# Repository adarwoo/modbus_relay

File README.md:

# Modbus Relay with EStop  #

## Introduction
This project features is a MODBUS RTU relays controller, which includes failsafe mode and an EStop.
It is aimed for industrial systems such as a CNC or equivalent.

The project comes complete with documentation, schematic, PCB, 3D part, artwork and source code.

For operational documentation, please check the complete [User Manual](docs/user_manual.md)

---

## Features summary

1. Standard DIN Rail mountable PCB
2. 3 relays - 9.4A 250VAC per output
3. Operational integrity minded
   * Uses a safety relay with force conduits and read back
   * Infeed voltage measurement with acceptable range
   * Communication watchdog
4. EStop management
   * Used for failsafe of the relay operation
      * Relay failure
      * Infeed voltage out-of-range
      * Communication loss
   * Externally controlled
     * Pulsed EStop
     * Resetable
     * Terminal
6. Operational statistics
   * Number of cycles
   * Running time
   * Fault codes

## Presentation of the hardware

<div style="text-align: center; position: relative;">

</div>

At the core of the relay is an AVR Tiny3227, an automotive grade MPU designed for harsh environment.
The MPU is clocked using the internal calibrated RC clock at 20MHz.

The relays are SISF brand used in safety critical applications.
They feature a forced conduit (so all contacts are driven by the same bar) and a dedicated read-back contact.
This allow validating the correct relay operations.
The relay are driven by small MOSFET. The read back features a contact scrubbing circuit as recommended by the manufacturer.

The modbus interface uses a RS485 driver LTC1785A (which features short protection) and transient suppressors.

The relay output features MOV suppressors for inductive loads.

The PCB can be placed in a DIN Rail PCB mount. 4 mounting screws can also be used.
A 3D cover is available to cover the whole PCBs. Together with the DIN rail mount assembly, the module should comply with IP2X.

### CAD files

The following files are available:
 * The [schematic](hw/modbus_relay.kicad.sch) edited with *KiCAD 9.1*
 * The [PCB](hw/modbus_relay.kicad.pcb) edited in *KiCAD 9.1*
 * The [BOM](hw/BOM.md) edited in *KiCAD 9.1*
 * The [Front plate artwork](hw/front_plate_graphics.svg) edited in LibreOffice Draw
 * [The front plate STL file](cad/Front%20Plate.3mf)
 * [LED holder STL file](cad/leds_spacer.STL)
 * [Spacer columns STL file](cad/3mm%2016mm.STL)
 * [Flex swtich membrane](cad/Flex%20switch%20membrane.STL)
 * [Flex retaining holder](cad/Flex%20Holder.STL)

For printing instructions, refer to [Printing the Files](#printing-the-files).

#### Printing the files

 * The case was printed in mate green PLA with PLA support material for the AVR port.
 * The flexible switch was printed in TPU.
 * The holder in black PLA.

#### Printing the front plate

 * The front was printed on an adhesive vinyl sticker at max resolution then cut to size.

> [!Note]
> You may need to adjust the dimension to account for non-linearity of the printer.

## Presentation of the software
The software is build on top of a small framework revolving around a simple reactor pattern.
The reactor allow for an arbitrary function to be notified from any context, and will execute when the CPU become available.
A simple priority system allow for reactor functions to be called in priority (to process data in a register).

A dedicated reactor pin allows measuring the worse compute time for any reactor function, which in turn, determine the worse
case latency. This allow garanteeing a real time operation throughout.
As such, the system does handle all asynchronous events in realtime with no delay, including all Modbus transaction, even at 115200 Bauds.
The jitter on the RS485 is almost null, and all replies are instantanous (4ms delay to allow for proper end of frame detection).

A python scripts is used to generates the final source for the modbus functions.

> [!TIP]
> This project could be reused for other Modbus devices. A modbus interface generator is provided that makes adding modbus commands simple.

## Application software
The application software is written in C++23 as it uses meta programming, constant expressions and concepts for efficient code.<br/>
A <i>docker</i> file is provided to create a build environment.</br>
The code fits the 32Kb flash space with plenty spare.

For build instructions, see [How to Build](#how-to-build).

## Hardware
The schematic and PCB have been edited in KiCad 9 and are supplied too.

## How to build
A docker container file is provided to recreated a full build environment.<br/>
The application can also be built in Microchip studio.<br/>
You will need a Linux shell, or WSL shell in Windows.
The tool 'gitman' is required as well as Docker. (docker-ce or else).

### Steps
```bash
# Clone this repo
$ git clone https://https://github.com/adarwoo/modbus_relay.git
$ cd modbus_relay
# Optional - install gitman
$ pipx install gitman
$ gitman update
$ make NDEBUG=1 # Optional, add ARCH=attiny1624 to suit you device
```

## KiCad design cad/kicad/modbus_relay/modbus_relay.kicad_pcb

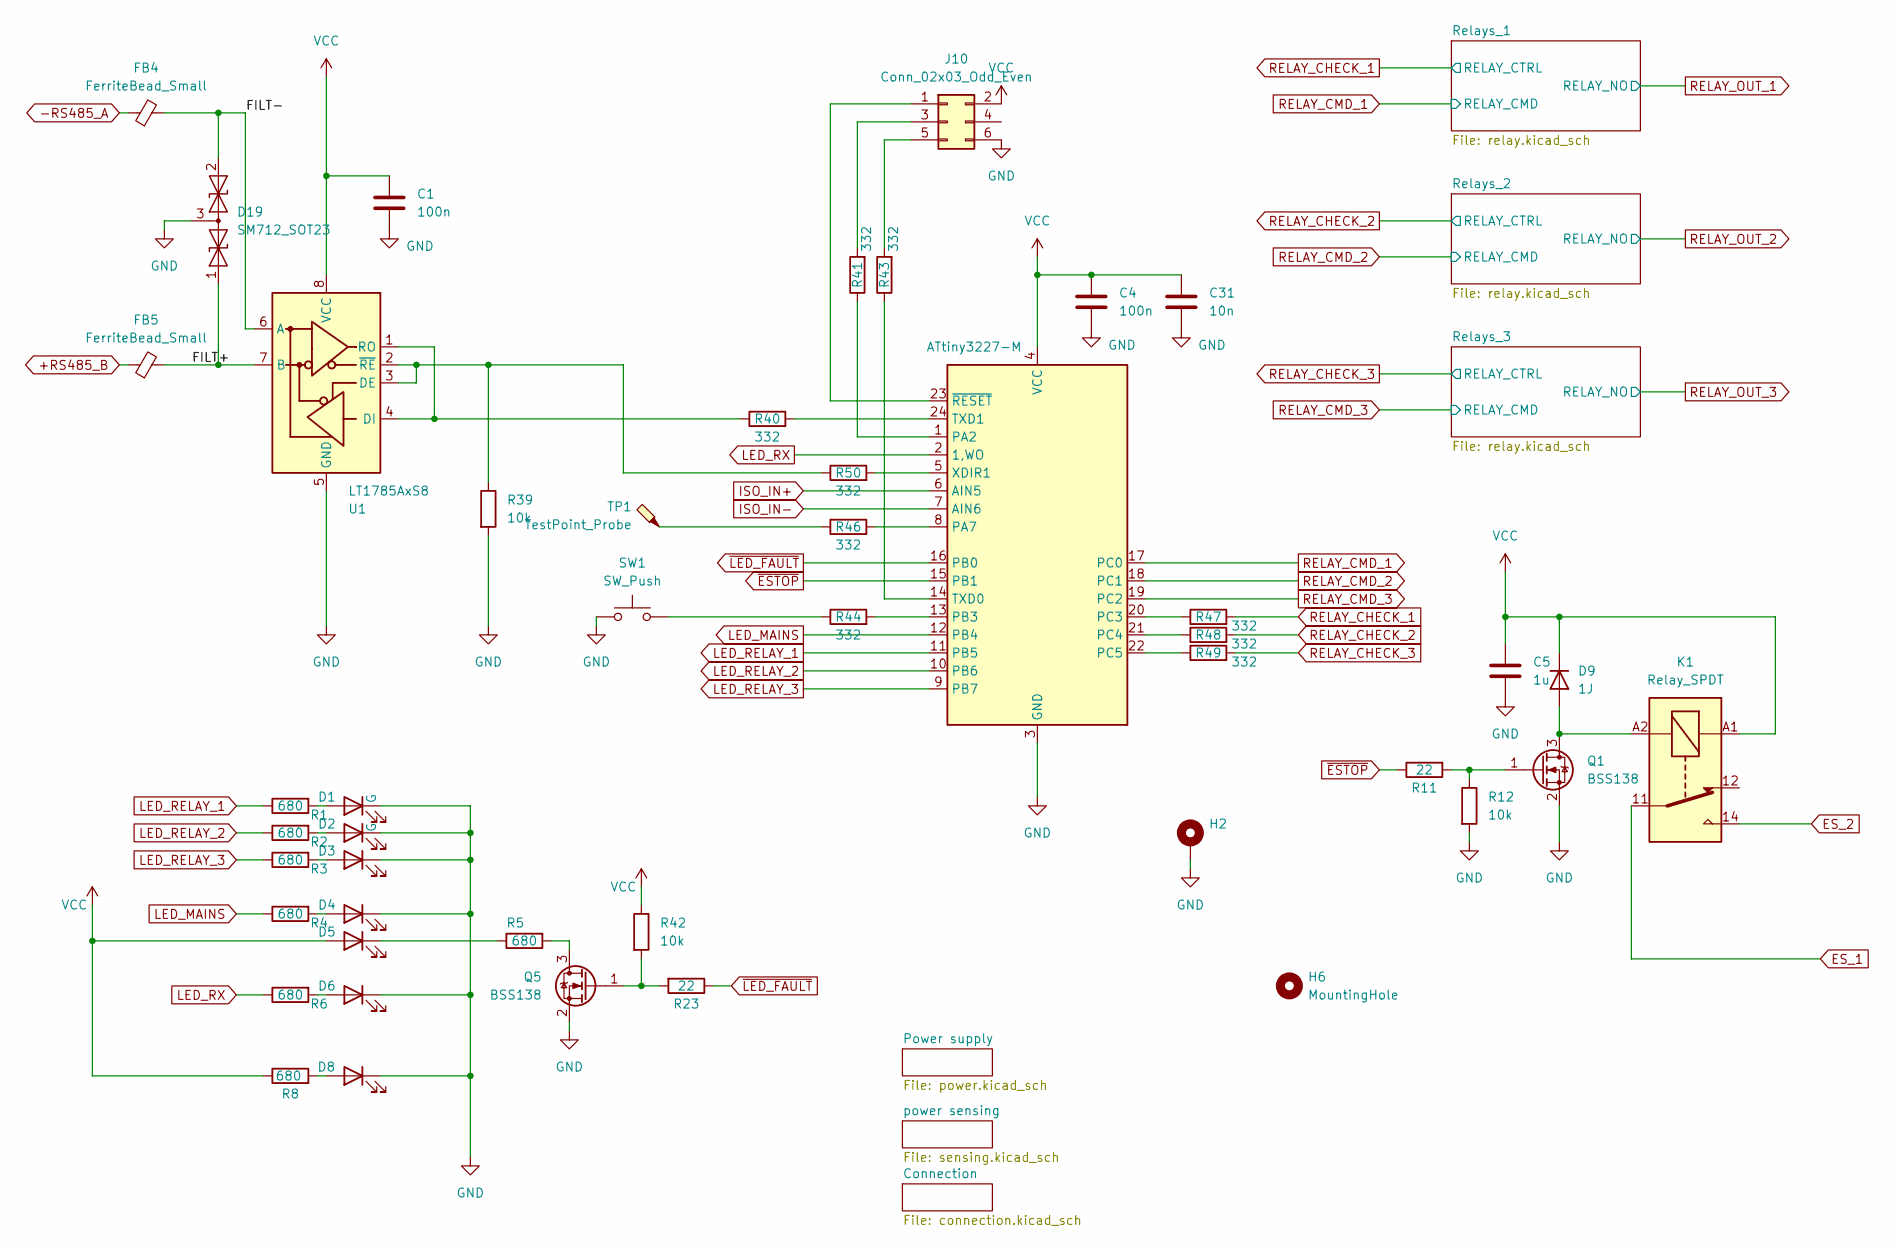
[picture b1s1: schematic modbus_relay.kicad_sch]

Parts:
C1, C4: 100n; C_0805_2012Metric_Pad1.18x1.45mm_HandSolder
C5: 1u; C_0805_2012Metric_Pad1.18x1.45mm_HandSolder
C31: 10n; C_0805_2012Metric_Pad1.18x1.45mm_HandSolder
D1, D2, D3, D4, D5, D6: G; LED_D3.0mm
D8: LED; LED_D3.0mm
D9: 1J; D_SOD-323_HandSoldering
D19: SM712_SOT23; SOT-23
FB4, FB5: FerriteBead_Small; L_0805_2012Metric
H2: MountingHole_Pad; MountingHole_3.2mm_M3_DIN965_Pad_TopBottom
H6: MountingHole; MountingHole_3.2mm_M3
J10: Conn_02x03_Odd_Even; PinHeader_2x03_P2.54mm_Vertical
K1: Relay_SPDT; Relay_SPDT_Finder_32.21-x000
Q1, Q5: BSS138; SOT-23
R1, R2, R3, R4, R5, R6, R8: 680; R_0805_2012Metric_Pad1.20x1.40mm_HandSolder
R11, R23: 22; R_0805_2012Metric_Pad1.20x1.40mm_HandSolder
R12, R39, R42: 10k; R_0805_2012Metric_Pad1.20x1.40mm_HandSolder
R40, R41, R43, R44, R46, R47, R48, R49, R50: 332; R_0805_2012Metric_Pad1.20x1.40mm_HandSolder
SW1: SW_Push; SW_PUSH_6mm_H4.3mm
TP1: TestPoint_Probe; TestPoint_Pad_D1.5mm
U1: LT1785AxS8; SOIC-8_3.9x4.9mm_P1.27mm
U2: ATtiny3227-M; QFN-24-1EP_4x4mm_P0.5mm_EP2.6x2.6mm

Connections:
+RS485_B: FB5.1; also elsewhere on the board
-RS485_A: FB4.1; also elsewhere on the board
/FILT+: D19.1 (A1), FB5.2, U1.7 (B)
/FILT-: D19.2 (A2), FB4.2, U1.6 (A)
ES_1: K1.11; also elsewhere on the board
ES_2: K1.14; also elsewhere on the board
GND: C1.2, C4.2, C5.2, C31.2, D1.1 (K), D2.1 (K), D3.1 (K), D4.1 (K), D6.1 (K), D8.1 (K), D19.3 (common), H2.1, J10.6, Q1.2 (S), Q5.2 (S), R12.2, R39.2, SW1.2, U1.5 (GND), U2.3 (GND), U2.25 (GND); also elsewhere on the board
ISO_IN+: U2.6 (AIN5); also elsewhere on the board
ISO_IN-: U2.7 (AIN6); also elsewhere on the board
LED_MAINS: R4.1, U2.12 (PB4)
LED_RELAY_1: R1.1, U2.11 (PB5)
LED_RELAY_2: R2.1, U2.10 (PB6)
LED_RELAY_3: R3.1, U2.9 (PB7)
LED_RX: R6.1, U2.2 (1,WO)
unnamed: D1.2 (A), R1.2
unnamed: D2.2 (A), R2.2
unnamed: D3.2 (A), R3.2
unnamed: D4.2 (A), R4.2
unnamed: D5.1 (K), R5.1
unnamed: D6.2 (A), R6.2
unnamed: D8.2 (A), R8.2
unnamed: D9.2 (A), K1.A2, Q1.3 (D)
unnamed: J10.1, U2.23 (~RESET)
unnamed: J10.3, R41.2
unnamed: J10.5, R43.2
unnamed: Q1.1 (G), R11.2, R12.1
unnamed: Q5.3 (D), R5.2
unnamed: Q5.1 (G), R23.2, R42.2
unnamed: R44.1, SW1.1
unnamed: R46.1, TP1.1
unnamed: R39.1, R50.1, U1.2 (~RE), U1.3 (DE)
unnamed: R40.1, U1.1 (RO), U1.4 (DI)
unnamed: R40.2, U2.24 (TXD1)
unnamed: R41.1, U2.1 (PA2)
unnamed: R50.2, U2.5 (XDIR1)
unnamed: R46.2, U2.8 (PA7)
unnamed: R43.1, U2.14 (TXD0)
unnamed: R44.2, U2.13 (PB3)
unnamed: R47.1, U2.20 (PC3)
unnamed: R48.1, U2.21 (PC4)
unnamed: R49.1, U2.22 (PC5)
RELAY_CHECK_1: R47.2; also elsewhere on the board
RELAY_CHECK_2: R48.2; also elsewhere on the board
RELAY_CHECK_3: R49.2; also elsewhere on the board
RELAY_CMD_1: U2.17 (PC0); also elsewhere on the board
RELAY_CMD_2: U2.18 (PC1); also elsewhere on the board
RELAY_CMD_3: U2.19 (PC2); also elsewhere on the board
VCC: C1.1, C4.1, C5.1, C31.1, D5.2 (A), D9.1 (K), J10.2, K1.A1, R8.1, R42.1, U1.8 (VCC), U2.4 (VCC); also elsewhere on the board
~ESTOP: R11.1, U2.15 (PB1)
~LED_FAULT: R23.1, U2.16 (PB0)

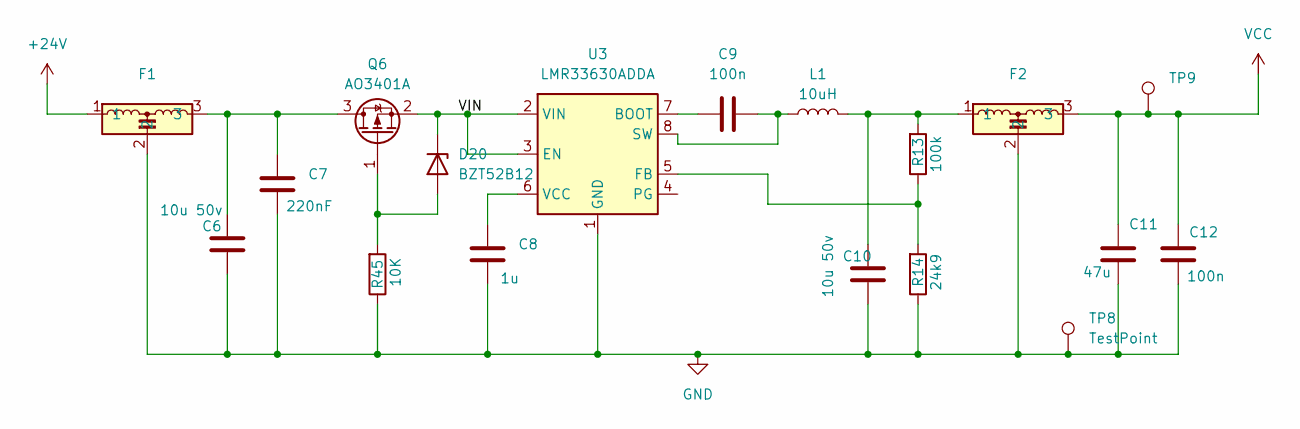
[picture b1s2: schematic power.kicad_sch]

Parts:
C6, C10: 10u 50v; C_1210_3225Metric_Pad1.33x2.70mm_HandSolder
C7: 220nF; C_0805_2012Metric_Pad1.18x1.45mm_HandSolder
C8: 1u; C_0805_2012Metric_Pad1.18x1.45mm_HandSolder
C9, C12: 100n; C_0805_2012Metric_Pad1.18x1.45mm_HandSolder
C11: 47u; C_1210_3225Metric_Pad1.33x2.70mm_HandSolder
D20: BZT52B12; D_SOD-123F
F1, F2: Murata_NFM61R
L1: 10uH; L_Bourns_SRP6060FA
Q6: AO3401A; SOT-23
R13: 100k; R_0805_2012Metric_Pad1.20x1.40mm_HandSolder
R14: 24k9; R_0805_2012Metric_Pad1.20x1.40mm_HandSolder
R45: 10K; R_0805_2012Metric_Pad1.20x1.40mm_HandSolder
TP8: TestPoint; TestPoint_Loop_D3.50mm_Drill0.9mm_Beaded
TP9: TestPoint; TestPoint_Pad_D1.5mm
U3: LMR33630ADDA; Texas_HSOP-8-1EP_3.9x4.9mm_P1.27mm_ThermalVias

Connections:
+24V: F1.1; also elsewhere on the board
/Power supply/VIN: D20.1 (K), Q6.2 (S), U3.2 (VIN), U3.3 (EN)
GND: C6.2, C7.2, C8.2, C10.2, C11.2, C12.1, F1.2, F2.2, R14.1, R45.1, TP8.1, U3.1 (GND), U3.9 (GND); also elsewhere on the board
unnamed: C10.1, F2.1, L1.2, R13.2
unnamed: D20.2 (A), Q6.1 (G), R45.2
unnamed: C6.1, C7.1, F1.3, Q6.3 (D)
unnamed: C9.1, U3.7 (BOOT)
unnamed: R13.1, R14.2, U3.5 (FB)
unnamed: C9.2, L1.1, U3.8 (SW)
unnamed: C8.1, U3.6 (VCC)
VCC: C11.1, C12.2, F2.3, TP9.1; also elsewhere on the board

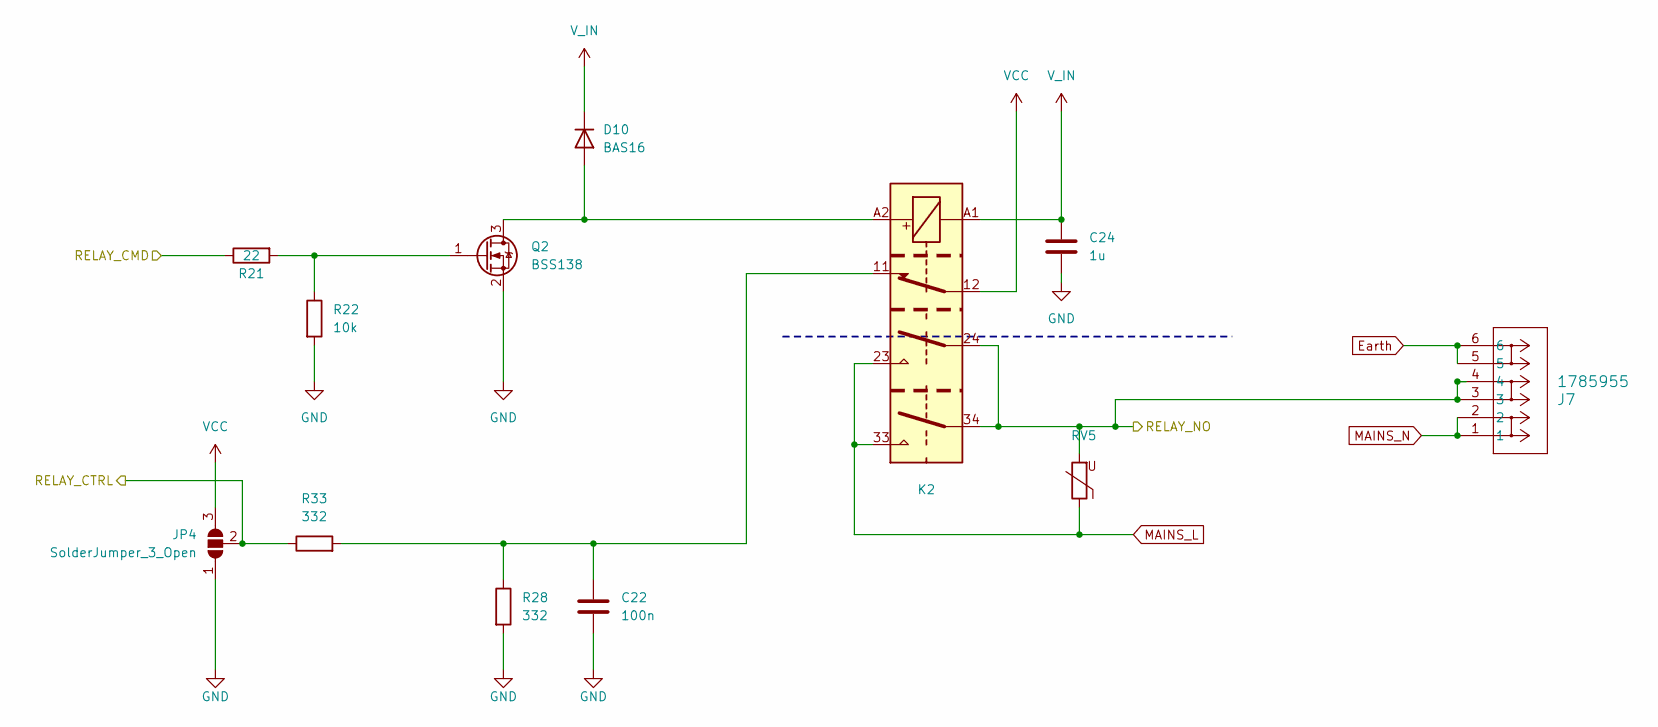
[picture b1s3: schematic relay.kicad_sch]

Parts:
C22: 100n; C_0805_2012Metric_Pad1.18x1.45mm_HandSolder
C24: 1u; C_0805_2012Metric_Pad1.18x1.45mm_HandSolder
D10: BAS16; D_SOD-323_HandSoldering
J7: 1785955; CONN_1943548
JP4: SolderJumper_3_Open; SolderJumper-3_P1.3mm_Open_RoundedPad1.0x1.5mm_NumberLabels
K2: SISF212
Q2: BSS138; SOT-23
R21: 22; R_0805_2012Metric_Pad1.20x1.40mm_HandSolder
R22: 10k; R_0805_2012Metric_Pad1.20x1.40mm_HandSolder
R28, R33: 332; R_0805_2012Metric_Pad1.20x1.40mm_HandSolder
RV5: 471K; MOV471

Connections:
Earth: J7.5, J7.6; also elsewhere on the board
GND: C22.2, C24.2, JP4.1 (A), Q2.2 (S), R22.2, R28.2; also elsewhere on the board
MAINS_L: K2.23, K2.33, RV5.1; also elsewhere on the board
MAINS_N: J7.1, J7.2; also elsewhere on the board
unnamed: C22.1, K2.11, R28.1, R33.2
unnamed: D10.2 (A), K2.A2, Q2.3 (D)
unnamed: Q2.1 (G), R21.2, R22.1
RELAY_CHECK_1: JP4.2 (C), R33.1; also elsewhere on the board
RELAY_CMD_1: R21.1; also elsewhere on the board
RELAY_OUT_1: J7.3, J7.4, K2.24, K2.34, RV5.2
VCC: JP4.3 (B), K2.12; also elsewhere on the board
V_IN: C24.1, D10.1 (K), K2.A1; also elsewhere on the board

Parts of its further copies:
C25, C28: 100n; C_0805_2012Metric_Pad1.18x1.45mm_HandSolder
C27, C30: 1u; C_0805_2012Metric_Pad1.18x1.45mm_HandSolder
D13, D16: BAS16; D_SOD-323_HandSoldering
J8, J12: 1785955; CONN_1943548
JP5, JP6: SolderJumper_3_Open; SolderJumper-3_P1.3mm_Open_RoundedPad1.0x1.5mm_NumberLabels
K3, K4: SISF212
Q3, Q4: BSS138; SOT-23
R26, R31: 22; R_0805_2012Metric_Pad1.20x1.40mm_HandSolder
R27, R32: 10k; R_0805_2012Metric_Pad1.20x1.40mm_HandSolder
R29, R30, R34, R35: 332; R_0805_2012Metric_Pad1.20x1.40mm_HandSolder
RV6, RV7: 471K; MOV471

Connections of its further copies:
Earth: J8.5, J8.6, J12.5, J12.6; also elsewhere on the board
GND: C25.2, C27.2, C28.2, C30.2, JP5.1 (A), JP6.1 (A), Q3.2 (S), Q4.2 (S), R27.2, R29.2, R30.2, R32.2; also elsewhere on the board
MAINS_L: K3.23, K3.33, K4.23, K4.33, RV6.1, RV7.1; also elsewhere on the board
MAINS_N: J8.1, J8.2, J12.1, J12.2; also elsewhere on the board
unnamed: C25.1, K3.11, R29.1, R34.2
unnamed: C28.1, K4.11, R30.1, R35.2
unnamed: D13.2 (A), K3.A2, Q3.3 (D)
unnamed: D16.2 (A), K4.A2, Q4.3 (D)
unnamed: Q3.1 (G), R26.2, R27.1
unnamed: Q4.1 (G), R31.2, R32.1
RELAY_CHECK_2: JP6.2 (C), R35.1; also elsewhere on the board
RELAY_CHECK_3: JP5.2 (C), R34.1; also elsewhere on the board
RELAY_CMD_2: R31.1; also elsewhere on the board
RELAY_CMD_3: R26.1; also elsewhere on the board
RELAY_OUT_2: J12.3, J12.4, K4.24, K4.34, RV7.2
RELAY_OUT_3: J8.3, J8.4, K3.24, K3.34, RV6.2
VCC: JP5.3 (B), JP6.3 (B), K3.12, K4.12; also elsewhere on the board
V_IN: C27.1, C30.1, D13.1 (K), D16.1 (K), K3.A1, K4.A1; also elsewhere on the board

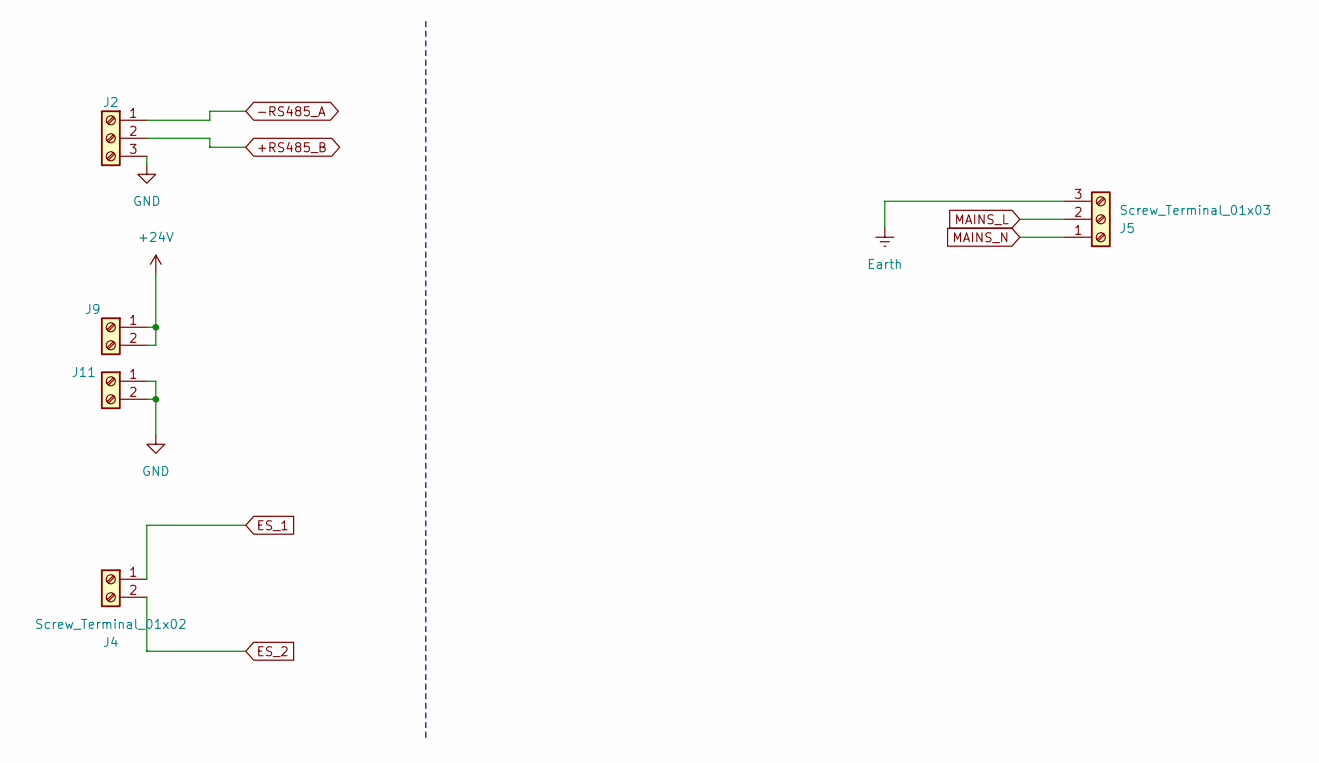
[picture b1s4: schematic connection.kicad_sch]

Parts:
J2: Screw_Terminal_01x03; PhoenixContact_MCV_1,5_3-G-3.81_1x03_P3.81mm_Vertical
J4, J9, J11: Screw_Terminal_01x02; PhoenixContact_MCV_1,5_2-G-3.81_1x02_P3.81mm_Vertical
J5: Screw_Terminal_01x03; PhoenixContact_MSTBVA_2,5_3-G-5,08_1x03_P5.08mm_Vertical

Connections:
+24V: J9.1, J9.2; also elsewhere on the board
+RS485_B: J2.2; also elsewhere on the board
-RS485_A: J2.1; also elsewhere on the board
ES_1: J4.1; also elsewhere on the board
ES_2: J4.2; also elsewhere on the board
Earth: J5.3; also elsewhere on the board
GND: J2.3, J11.1, J11.2; also elsewhere on the board
MAINS_L: J5.2; also elsewhere on the board
MAINS_N: J5.1; also elsewhere on the board

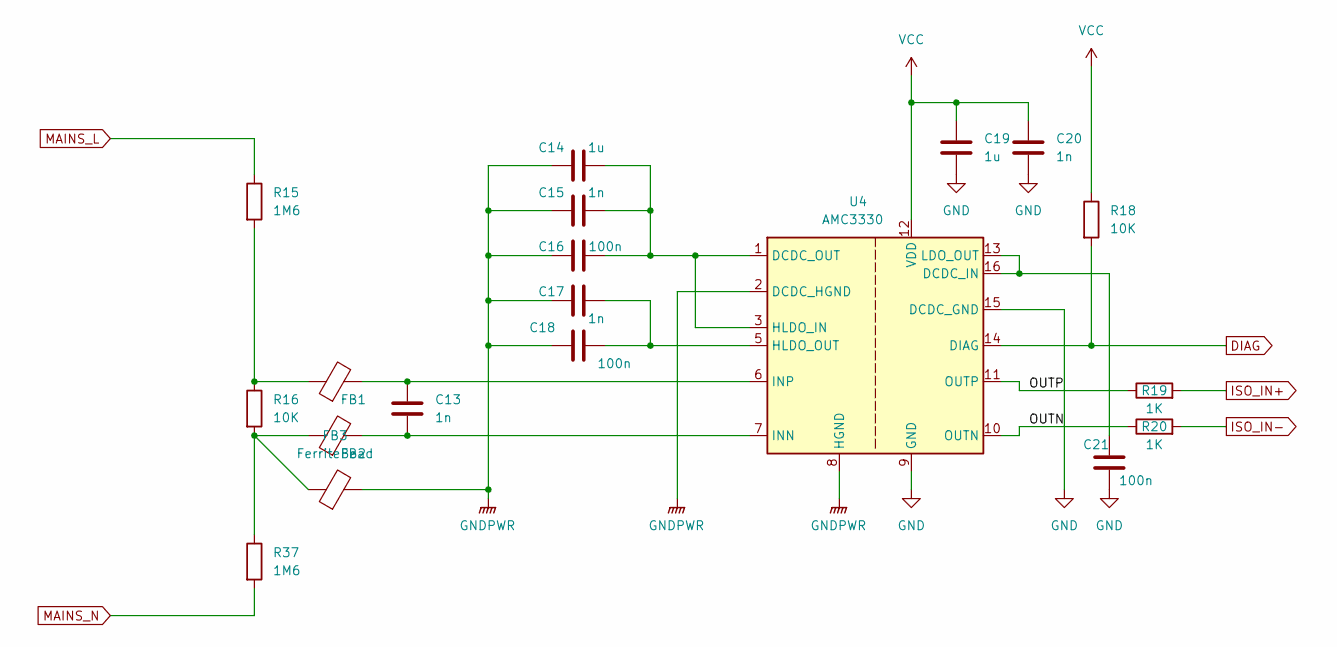
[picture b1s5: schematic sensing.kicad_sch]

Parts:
C13, C15, C17, C20: 1n; C_0805_2012Metric_Pad1.18x1.45mm_HandSolder
C14, C19: 1u; C_0805_2012Metric_Pad1.18x1.45mm_HandSolder
C16, C18, C21: 100n; C_0805_2012Metric_Pad1.18x1.45mm_HandSolder
FB1, FB2, FB3: FerriteBead; L_0805_2012Metric
R15, R37: 1M6; R_1206_3216Metric_Pad1.30x1.75mm_HandSolder
R16, R18: 10K; R_0805_2012Metric_Pad1.20x1.40mm_HandSolder
R19, R20: 1K; R_0805_2012Metric_Pad1.20x1.40mm_HandSolder
U4: AMC3330; SOIC-16W_7.5x10.3mm_P1.27mm

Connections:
/power sensing/OUTN: R20.1, U4.10 (OUTN)
/power sensing/OUTP: R19.1, U4.11 (OUTP)
DIAG: R18.2, U4.14 (DIAG)
GND: C19.1, C20.1, C21.1, U4.9 (GND), U4.15 (DCDC_GND); also elsewhere on the board
GNDPWR: C14.1, C15.1, C16.1, C17.1, C18.1, FB3.2, U4.2 (DCDC_HGND), U4.8 (HGND)
ISO_IN+: R19.2; also elsewhere on the board
ISO_IN-: R20.2; also elsewhere on the board
MAINS_L: R15.1; also elsewhere on the board
MAINS_N: R37.2; also elsewhere on the board
unnamed: FB1.1, R15.2, R16.1
unnamed: FB2.1, FB3.1, R16.2, R37.1
unnamed: C21.2, U4.13 (LDO_OUT), U4.16 (DCDC_IN)
unnamed: C14.2, C15.2, C16.2, U4.1 (DCDC_OUT), U4.3 (HLDO_IN)
unnamed: C17.2, C18.2, U4.5 (HLDO_OUT)
unnamed: C13.1, FB2.2, U4.7 (INN)
unnamed: C13.2, FB1.2, U4.6 (INP)
VCC: C19.2, C20.2, R18.1, U4.12 (VDD); also elsewhere on the board

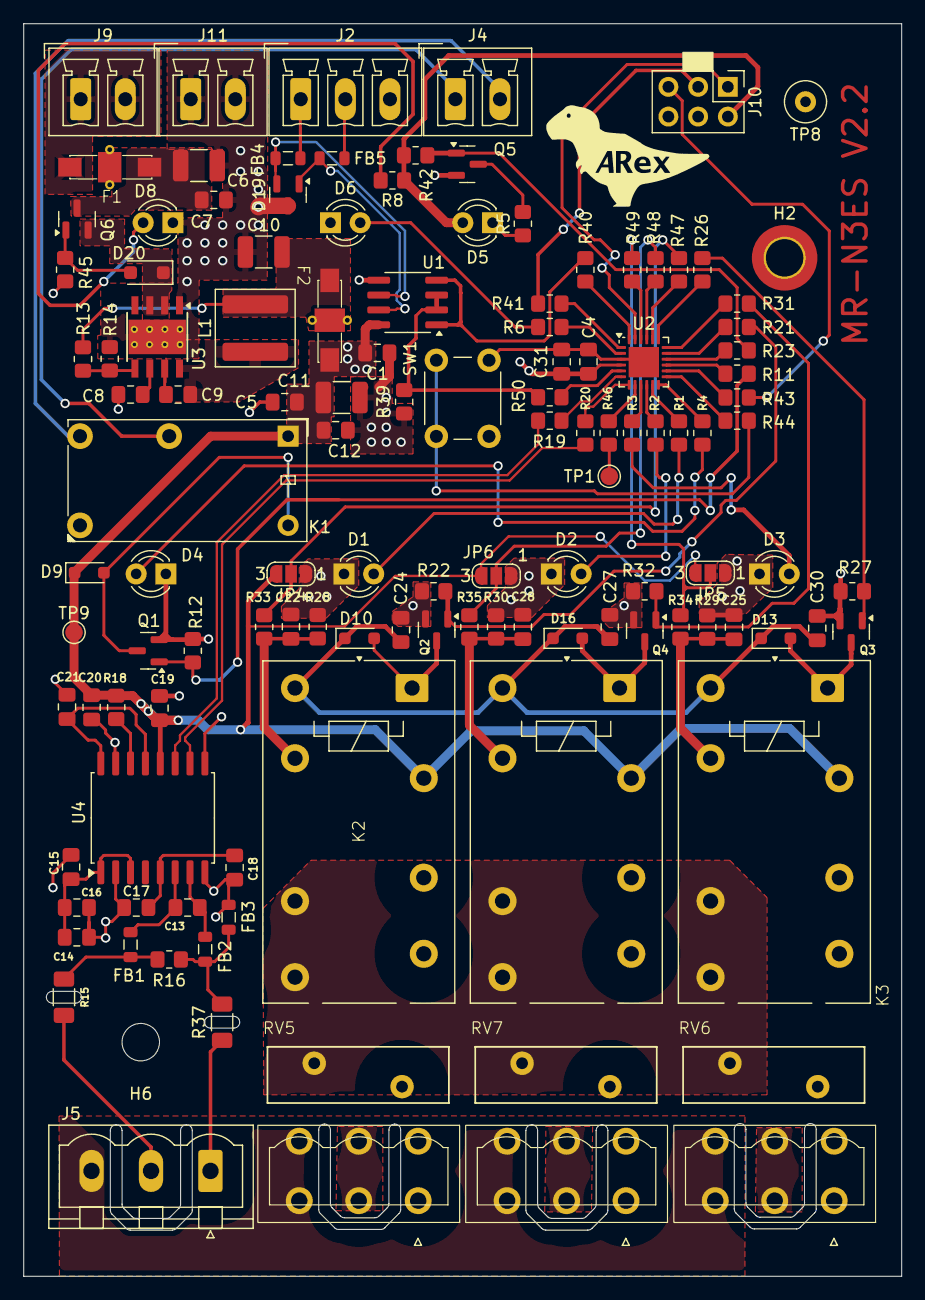
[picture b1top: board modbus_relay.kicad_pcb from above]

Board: 2 copper layers, 75.0 x 107.0 mm, 124 parts (0 on the bottom side), 86 nets.

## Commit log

2024-12-14 Initial addition of all files
2024-12-14 Enforce ignore
2024-12-14 Compiling with ASX
2024-12-14 Clean up
2024-12-15 Switching to gitman
2024-12-15 Working with all commands
2024-12-16 Adding the KiCad files
2024-12-16 Reverting to 115200
2024-12-16 Etl not used
2024-12-17 Added user manual for the configuration
2025-01-02 All done. Validation to follow
2025-01-02 Fixed baud setting. Using a 1/100th value
2025-01-02 Adding front pic
2025-01-02 Update README.md
    Added pictures side by side
2025-01-28 Add attributes to see if it fixes the view issue
2025-01-28 Update README.md
    Pictures uploaded as assets
2025-01-28 Update README.md
    Uploaded images direct in git resized
2025-01-31 Cleanup
2025-04-20 Fixed build with latest ASX
2025-04-20 clean rules
2025-05-04 Typo
2025-05-08 Added comments
2025-05-08 Last change before branching
2025-05-09 Reformat using coherent format
2025-05-13 Processing of the ingress voltage
2025-05-13 New definitions for the estop card
2025-05-13 Moving to a constexpr version
2025-05-13 Start of workl. In progress
2025-05-13 Work in progress. Need to sense the button to switch to the config mode
2025-05-13 cosmetic only
2025-05-13 Got it to compile - but need to revisit the code
2025-05-13 Up to date
2025-05-13 Automatic update of README.md
2025-05-13 Automatic update datagram.conf.py
2025-05-15 New iopiort wired
2025-05-16 Automatic Update ingress.cpp
2025-05-16 Ready to be tested
2025-05-18 Debugging and fixing as test progress
2025-05-19 Update README.md
    Automatic update
2025-05-19 Picture of the new relay added
2025-05-22 Added front plate graphics
2025-06-03 Work in progress
2025-06-07 Fixed all the registers to be readable in 1 go
2025-06-07 Registers index now ok
2025-06-07 Added table of content
2025-06-07 Added CAD files and bom
2025-06-07 Added printed files
2025-06-07 New 3d view
2025-06-07 Clarify use of command 16
2025-06-08 On-going sync with the documentation
2025-06-08 Updated TOC
2025-06-08 Compiling
2025-06-10 Renamed modbus in net to avoid conflict
2025-06-10 on-going work
2025-06-10 Leds are self managed now
2025-06-10 Split the documentation
2025-06-10 oops wrong place
2025-06-15 Code should be complete and inline with the latest hardware change and the user manual. Tests to follow
2025-06-15 Re-alinged all with the last user manual
2025-06-15 For studio
2025-06-18 Renamed files. Changed the hardware to avoid killing the modbus on startup. Tests are in progress
2025-06-18 Work in progress - but core is running
2025-06-18 Fixed the recovery mode.
2025-06-19 Adding a flow chart for the recovery
2025-06-20 Invert is gone because inverting when the fail safe is to open makes no sense
2025-06-20 Cleaned directory structure
2025-06-23 Need to set the buffer size for outgoing messages
2025-06-23 Aligning with the doc
2025-06-23 Overhaul of the recovery and management of the baud rate and uart
2025-06-23 Lining with doc
2025-06-25 Added description of the filtering
2025-06-25 Filter is given in 1/10s
2025-06-25 Reworked the relay to include the filtering.
2025-06-27 ALigning with spec and testing
2025-07-02 Fixed the filter
2025-07-16 Fixed the board for the ADC to work. Made the AC and DC measurements work. Added ulog
2025-07-18 Automatic system update
2025-07-30 Providing identification command
2025-07-30 Faults are a bitmask of faults
2025-07-30 Update of kicad and project files
2025-09-01 Double sided version
2025-09-07 New PCBs fixed and tested. Clean defs
2025-09-22 Automatic commit
2025-10-05 Fixing all during tests
2025-10-05 Still debugging. ULog mystery looks fixed (many many many added issues)
2025-10-05 lasest
2025-10-13 Cleaned the LED section. Aligning with the code and tests
2025-10-13 New faceplate with notches
2025-10-13 Using the same type of the config and input. So the config now has a none type for infeed type which means - don't care
2025-10-13 Reworking to match documentation. Test ongoing
2025-10-13 Adding fault management as a state of the system
2025-10-13 Added some ULOG
2025-10-13 Aligning with the documentation.
2025-10-13 Aligning with documentation. A EStop fault should flash - it must be seen
2025-10-13 ULog added to trace
2025-10-13 MErging input type with the cfg
2025-10-13 Init the config to spot boot errors
2025-10-13 Allow external shell history
2025-10-18 Changes follow validation still on-going
2025-10-18 Changes following validation
2025-10-19 Fixed the V_IN VIN label issue
2025-10-23 Automatic daily commit
2025-11-08 Fixed recovery. Added logs. Working overall
2025-11-12 Switching to ulog component
2025-11-13 Added more files
2025-12-08 Improved front plate
2025-12-09 sync
2026-01-03 Fixed z corssing detect
2026-01-09 Reorder to get high prior reactor registered first
2026-01-09 Lastest microchip studio file
2026-01-09 Allow debug with a deeper queue
